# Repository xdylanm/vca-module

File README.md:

# Dual VCA

A dual VCA module based on the LM13700 OTA in a Eurorack format.

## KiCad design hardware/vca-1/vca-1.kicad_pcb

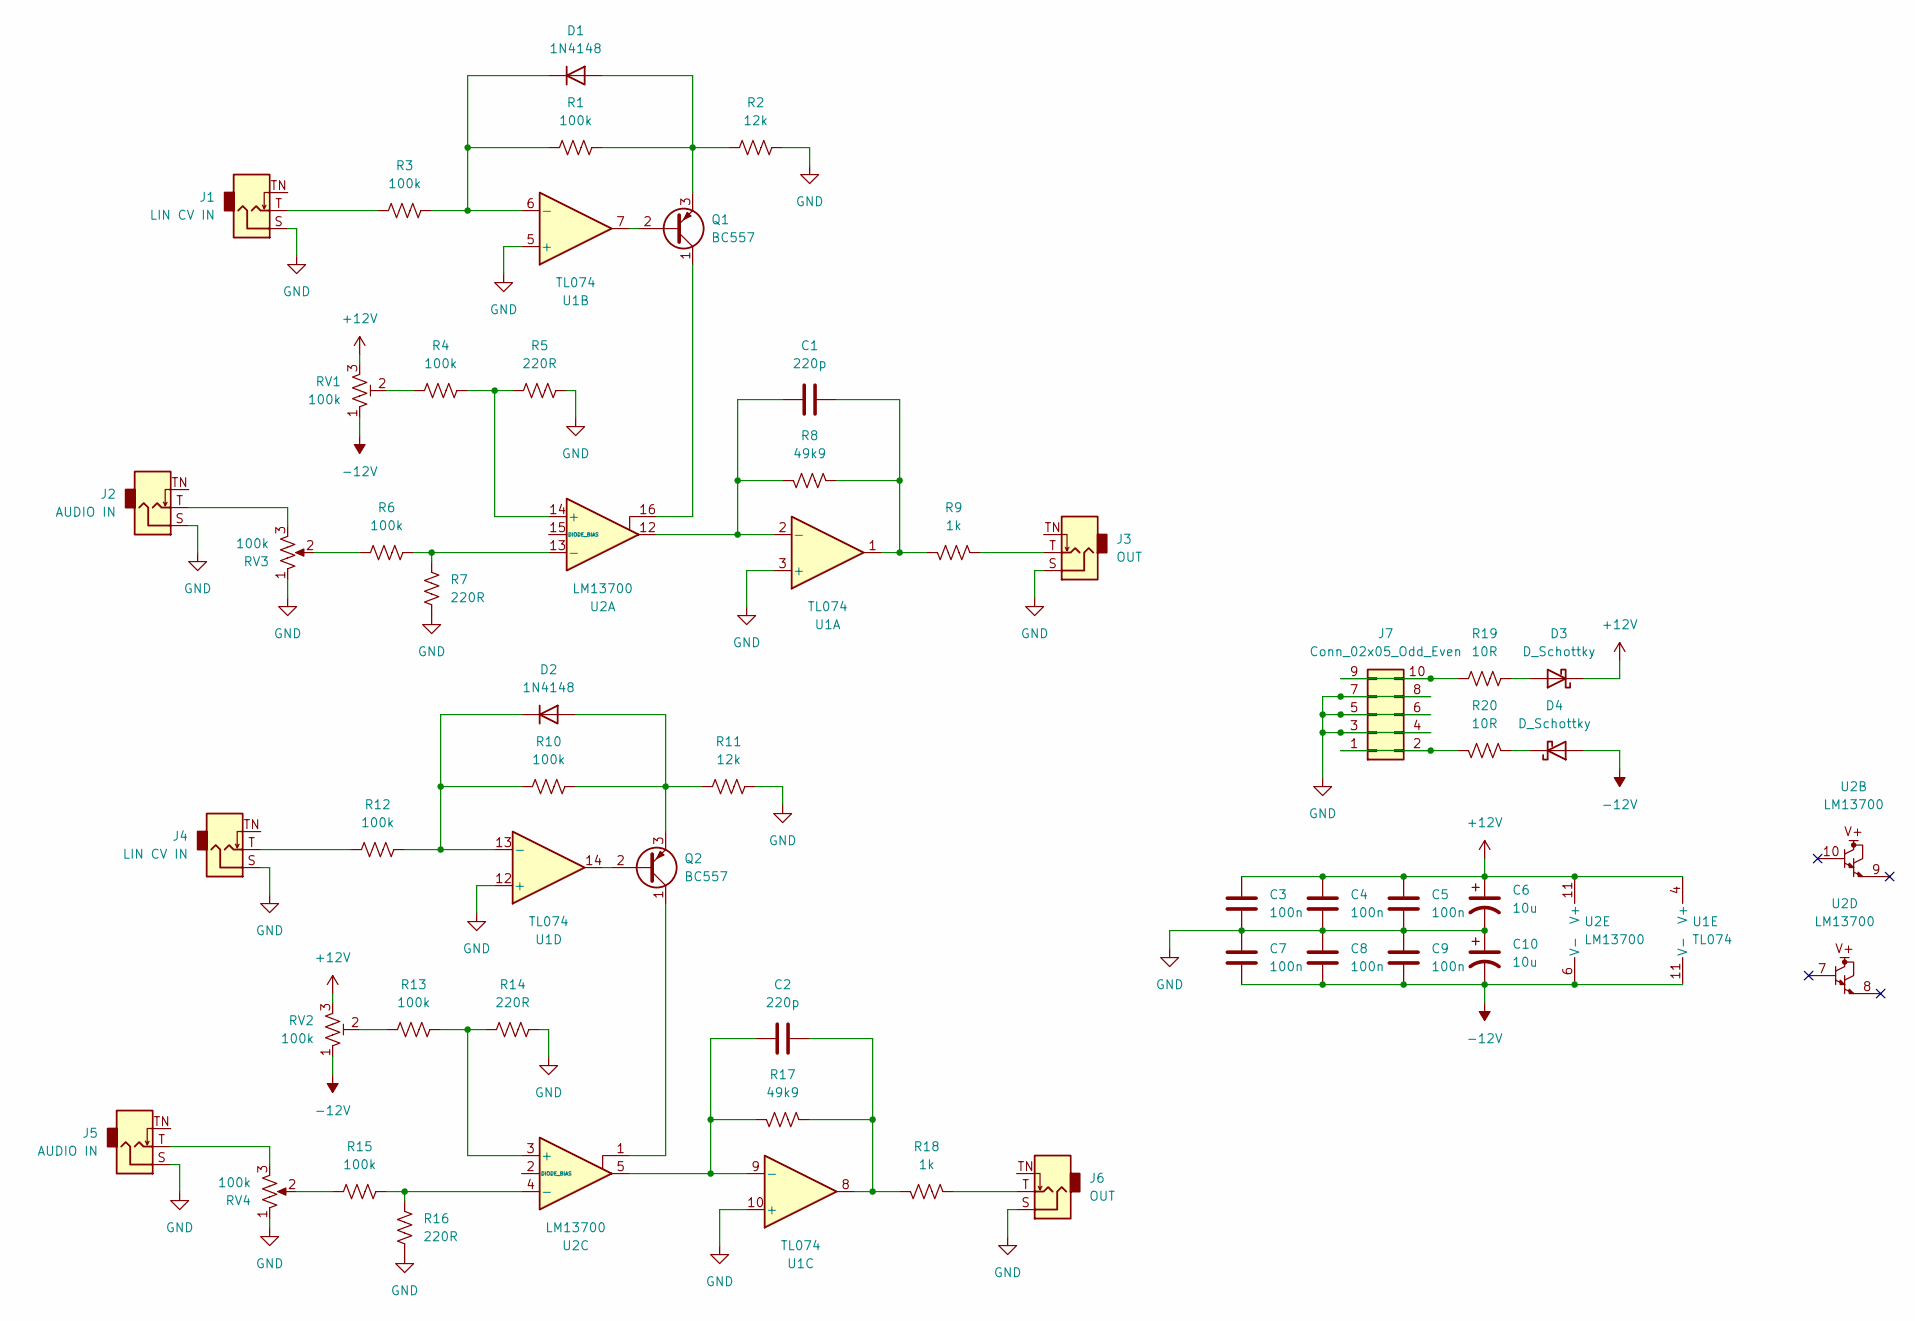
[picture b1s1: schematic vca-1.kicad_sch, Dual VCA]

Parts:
C1, C2: 220p; C_Disc_D4.3mm_W1.9mm_P5.00mm
C3, C4, C5, C7, C8, C9: 100n; C_Disc_D4.3mm_W1.9mm_P5.00mm
C6, C10: 10u; CP_Radial_D5.0mm_P2.50mm
D1, D2: 1N4148; D_DO-35_SOD27_P7.62mm_Horizontal
D3, D4: D_Schottky; D_DO-41_SOD81_P2.54mm_Vertical_KathodeUp
J1, J4: LIN CV IN; Jack_3.5mm_QingPu_WQP-PJ323M_Horizontal
J2, J5: AUDIO IN; Jack_3.5mm_QingPu_WQP-PJ323M_Horizontal
J3, J6: OUT; Jack_3.5mm_QingPu_WQP-PJ323M_Horizontal
J7: Conn_02x05_Odd_Even; IDC-Header_2x05_P2.54mm_Horizontal
Q1, Q2: BC557; TO-92_Inline_Wide
R1, R4, R10, R13: 100k; R_Axial_DIN0204_L3.6mm_D1.6mm_P2.54mm_Vertical
R2, R11: 12k; R_Axial_DIN0204_L3.6mm_D1.6mm_P2.54mm_Vertical
R3, R6, R12: 100k; R_Axial_DIN0204_L3.6mm_D1.6mm_P7.62mm_Horizontal
R5, R7, R14, R16: 220R; R_Axial_DIN0204_L3.6mm_D1.6mm_P2.54mm_Vertical
R8, R17: 49k9; R_Axial_DIN0204_L3.6mm_D1.6mm_P2.54mm_Vertical
R9, R18: 1k; R_Axial_DIN0204_L3.6mm_D1.6mm_P7.62mm_Horizontal
R15: 100k; R_Axial_DIN0207_L6.3mm_D2.5mm_P10.16mm_Horizontal
R19, R20: 10R; R_Axial_DIN0204_L3.6mm_D1.6mm_P2.54mm_Vertical
RV1, RV2: 100k; Potentiometer_Bourns_3296W_Vertical
RV3, RV4: 100k; Potentiometer_Bourns_PTV09A-2_Single_Horizontal
U1: TL074; DIP-14_W7.62mm_Socket
U2: LM13700; SOIC-16_3.9x9.9mm_P1.27mm

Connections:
+12V: C3.1, C4.1, C5.1, C6.1, D3.1 (K), RV1.3, RV2.3, U1.4 (V+), U2.11 (V+)
-12V: C7.2, C8.2, C9.2, C10.2, D4.2 (A), RV1.1, RV2.1, U1.11 (V-), U2.6 (V-)
GND: C3.2, C4.2, C5.2, C6.2, C7.1, C8.1, C9.1, C10.1, J1.S, J2.S, J3.S, J4.S, J5.S, J6.S, J7.3, J7.4, J7.5, J7.6, J7.7, J7.8, R2.1, R5.1, R7.1, R11.1, R14.1, R16.1, RV3.1, RV4.1, U1.3 (+), U1.5 (+), U1.10 (+), U1.12 (+)
unnamed: C1.2, R8.2, R9.1, U1.1
unnamed: C2.2, R17.2, R18.1, U1.8
unnamed: D1.2 (A), Q1.3 (E), R1.1, R2.2
unnamed: D1.1 (K), R1.2, R3.1, U1.6 (-)
unnamed: D2.2 (A), Q2.3 (E), R10.1, R11.2
unnamed: D2.1 (K), R10.2, R12.1, U1.13 (-)
unnamed: D3.2 (A), R19.2
unnamed: D4.1 (K), R20.2
unnamed: J1.T, R3.2
unnamed: J2.T, RV3.3
unnamed: J3.T, R9.2
unnamed: J4.T, R12.2
unnamed: J5.T, RV4.3
unnamed: J6.T, R18.2
unnamed: J7.1, J7.2, R20.1
unnamed: J7.9, J7.10, R19.1
unnamed: Q1.2 (B), U1.7
unnamed: Q1.1 (C), U2.16
unnamed: Q2.2 (B), U1.14
unnamed: Q2.1 (C), U2.1
unnamed: R4.2, RV1.2
unnamed: R6.2, RV3.2
unnamed: R13.2, RV2.2
unnamed: R15.2, RV4.2
unnamed: C1.1, R8.1, U1.2 (-), U2.12
unnamed: C2.1, R17.1, U1.9 (-), U2.5
unnamed: R4.1, R5.2, U2.14 (+)
unnamed: R6.1, R7.2, U2.13 (-)
unnamed: R13.1, R14.2, U2.3 (+)
unnamed: R15.1, R16.2, U2.4 (-)

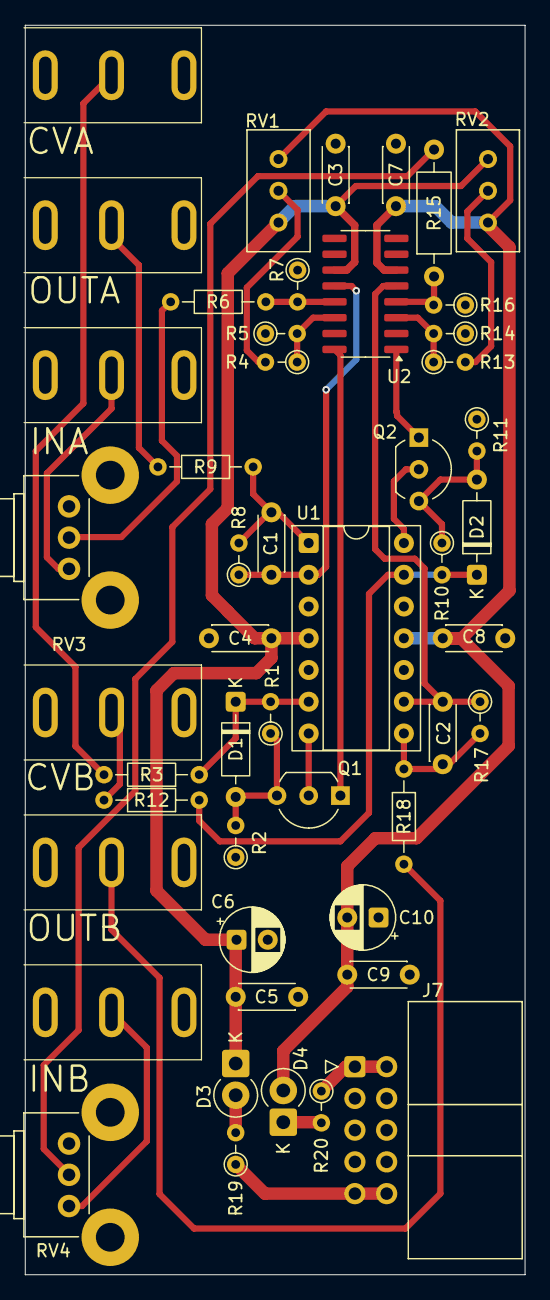
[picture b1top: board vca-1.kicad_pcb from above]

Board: 2 copper layers, 40.0 x 100.0 mm, 49 parts (0 on the bottom side), 33 nets.

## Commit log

2025-06-19 First version of linearly controlled dual VCA
2025-06-20 Added a level pot on the audio inputs, v1.1
2025-10-31 VCA face plate and doc updates
2025-10-31 sketch for v2 VCA (WIP)
2025-10-31 Migrated to mkdocs/material
2025-10-31 unity gain at 5V
2025-10-31 Updated component values for unity gain at 8V CV in to match ADSR
2025-10-31 Clean up and adding notebook with calculations
2025-11-04 Updated schematic values based on testing. Updated docs with measurements from board.
2025-11-05 Updated docs with image of VCA

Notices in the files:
hardware/vca-1/vca-1.kicad_pcb:
CC BY-SA 4.0
idyllm CC BY-SA 4.0
